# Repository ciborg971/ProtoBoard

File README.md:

# ProtoBoard V0.2

A small board (48 x 56 mm) for great gloves !

* Still a work in progress, current version does NOT work * 

# Features

## Pros :
- ESP32S3 dual core
- Small (48x56 mm)
- Power from 2S to 4S lipo (accept 6.5 volt up to 20 volt)
- Can use Wifi (doesnt use ADC2)
- 16 ADC input
- RGB Header
- 5V 5A for Servo for up to 5 Servo
- Support up to 7 LRA
- Battery protection (integrated BMS : overcharge, overdischarge and overcurrent protection)
- Battery level (via voltage divider)
- Cheap to build
- Use 2.54 mm header
- USB C for programming (The board CANNOT be powered via USB)

## Cons :
- Compoment on both side => more expensive to produce in small quantity in pcb fab (bottom side have easy to solder components)
- Doesnt charge the battery
- PCB is 4 layer (a bit more expensive than 2 layer PCB)

## Buy the PCB

*This design does NOT work right now, do NOT buy it unless you can debug it by yourself*
You can buy the board via PCBWay using the file ProtoBoard.kicad_pcb.zip and the BOM ProtoBoard.xlsx.

## TODO

- Add pinout

## Sponsors

This project is sponsored by PCBWay, thanks to them for their quality PCB + assembly !

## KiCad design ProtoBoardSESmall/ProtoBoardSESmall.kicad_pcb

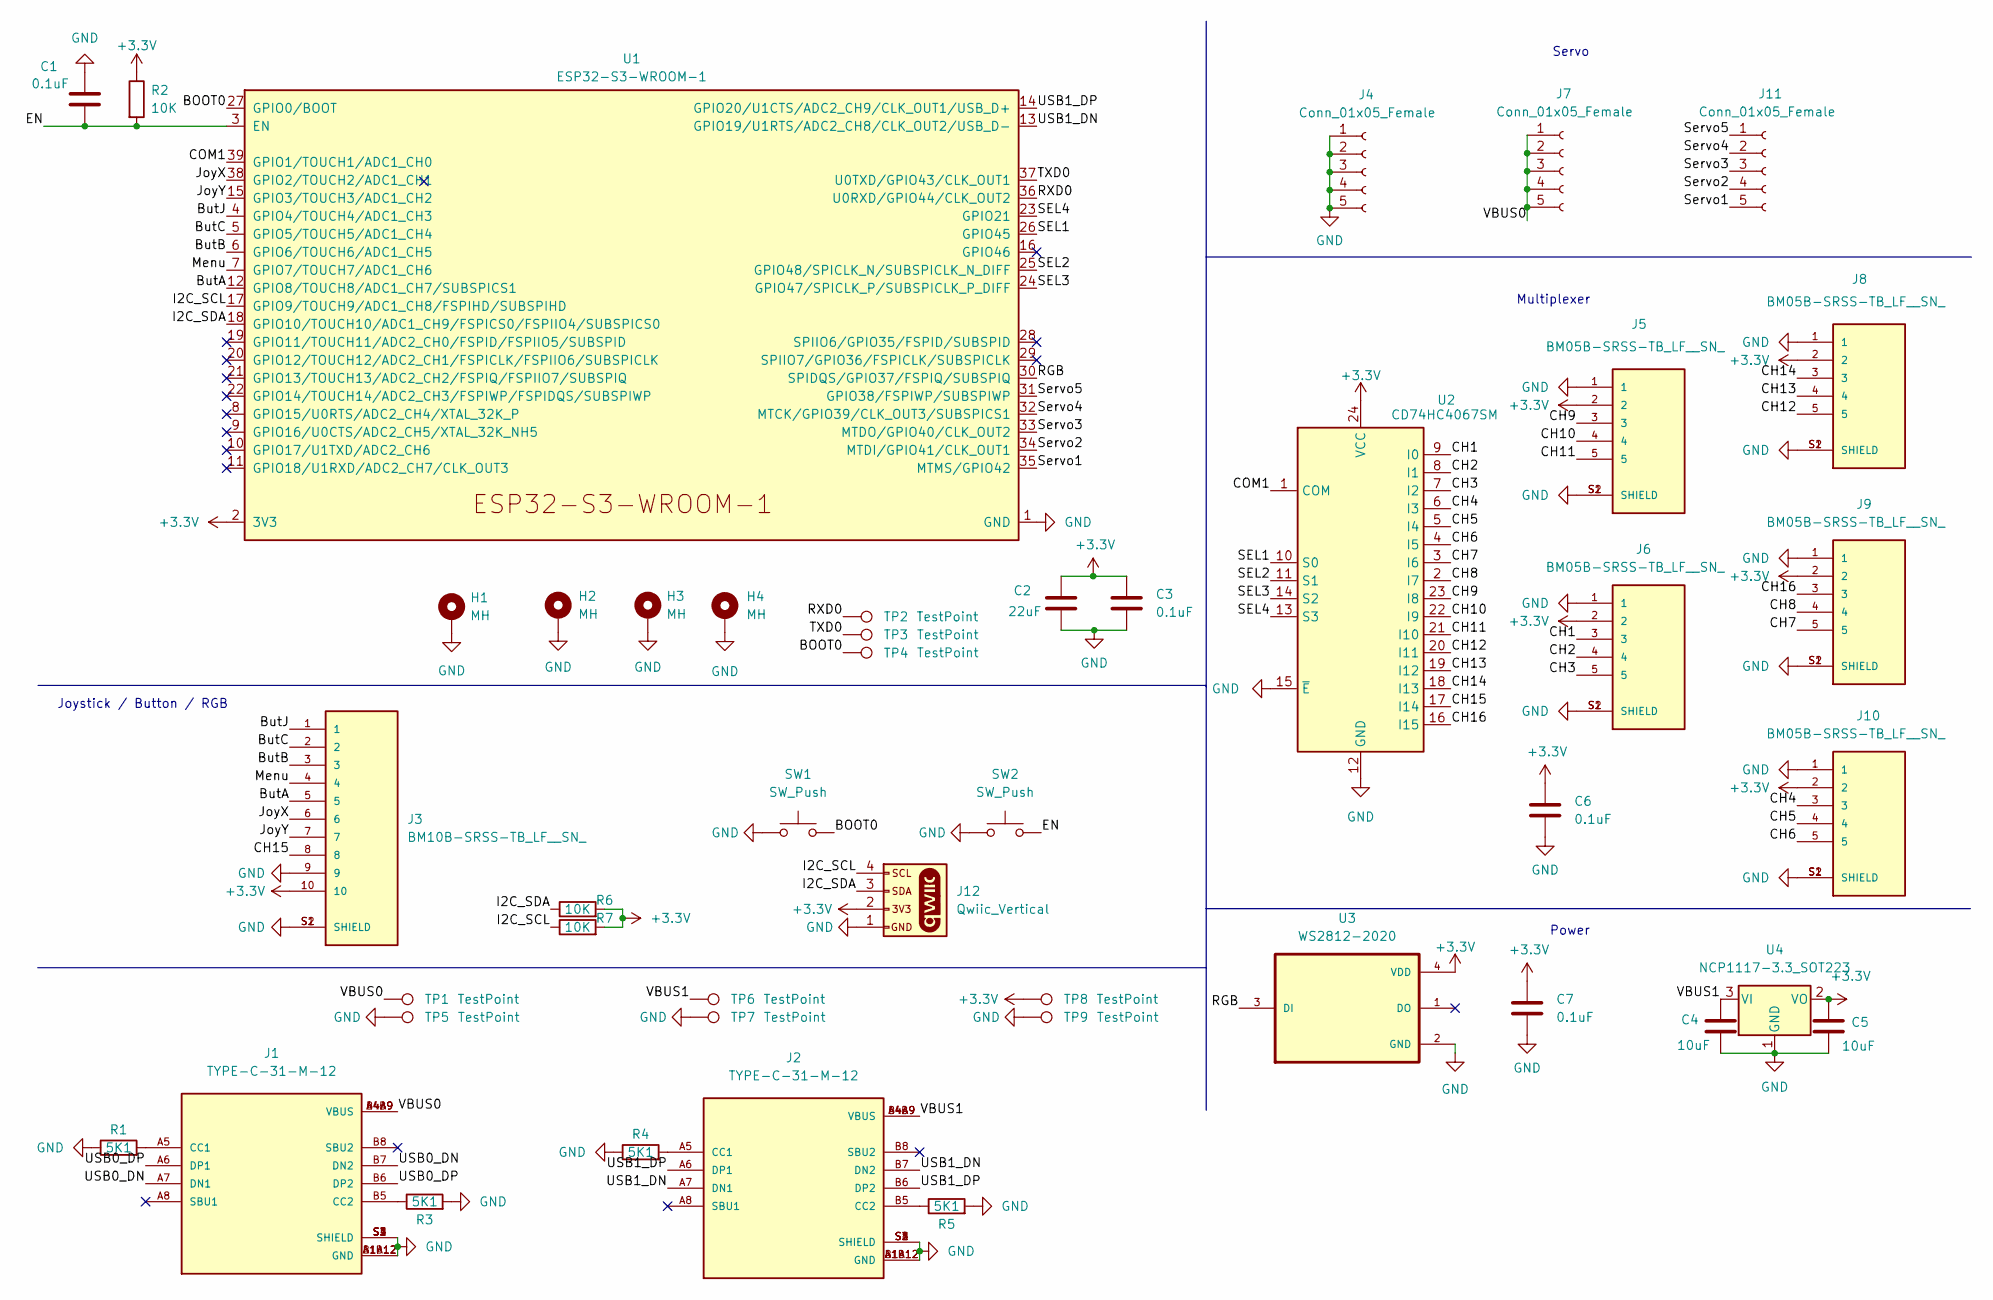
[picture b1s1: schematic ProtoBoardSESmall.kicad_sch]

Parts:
C1, C3, C6, C7: 0.1uF; C_0402_1005Metric; LCSC C129131
C2: 22uF; C_0402_1005Metric; LCSC C415703
C4, C5: 10uF; C_0402_1005Metric; LCSC C315248
H1, H2, H3, H4: MH; MountingHole_2.2mm_M2
J1, J2: TYPE-C-31-M-12; HRO_TYPE-C-31-M-12; PARTREV A; LCSC C165948
J3: BM10B-SRSS-TB_LF__SN_; JST_BM10B-SRSS-TB_LF__SN_; LCSC C160396
J4, J7, J11: Conn_01x05_Female; PinHeader_1x05_P2.54mm_Vertical; LCSC C492404
J5, J6, J8, J9, J10: BM05B-SRSS-TB_LF__SN_; JST_BM05B-SRSS-TB_LF__SN_; LCSC C160391
J12: Qwiic_Vertical; JST04_1MM_Vertical; LCSC C160390
R1, R3, R4, R5: 5K1; R_0402_1005Metric; LCSC C105872
R2: 10K; R_0402_1005Metric; LCSC C427247
R6, R7: 10K; R_0402_1005Metric; LCSC C60490
SW1, SW2: SW_Push; SW_Push_1P1T_NO_CK_KMR2; LCSC C221678
TP1, TP2, TP3, TP4, TP5, TP6, TP7, TP8, TP9: TestPoint; TestPoint_Pad_D1.5mm
U1: ESP32-S3-WROOM-1; LCSC C2913198
U2: CD74HC4067SM; SSOP-24_5.3x8.2mm_P0.65mm; LCSC C496123
U3: WS2812-2020; LED_WS2812-2020; PARTREV V1.3; LCSC C965555
U4: NCP1117-3.3_SOT223; SOT-223-3_TabPin2; LCSC C146799

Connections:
+3V3: C2.1, C3.1, C5.1, C6.1, C7.1, J3.10, J5.2, J6.2, J8.2, J9.2, J10.2, J12.2, R2.1, R6.2, R7.2, TP8.1, U1.2 (3V3), U2.24 (VCC), U3.4 (VDD), U4.2 (VO)
/BOOT0: SW1.2, TP4.1, U1.27 (GPIO0/BOOT)
/ButA: J3.5, U1.12 (GPIO8/TOUCH8/ADC1_CH7/SUBSPICS1)
/ButB: J3.3, U1.6 (GPIO6/TOUCH6/ADC1_CH5)
/ButC: J3.2, U1.5 (GPIO5/TOUCH5/ADC1_CH4)
/ButJ: J3.1, U1.4 (GPIO4/TOUCH4/ADC1_CH3)
/CH1: J6.3, U2.9 (I0)
/CH2: J6.4, U2.8 (I1)
/CH3: J6.5, U2.7 (I2)
/CH4: J10.3, U2.6 (I3)
/CH5: J10.4, U2.5 (I4)
/CH6: J10.5, U2.4 (I5)
/CH7: J9.5, U2.3 (I6)
/CH8: J9.4, U2.2 (I7)
/CH9: J5.3, U2.23 (I8)
/CH10: J5.4, U2.22 (I9)
/CH11: J5.5, U2.21 (I10)
/CH12: J8.5, U2.20 (I11)
/CH13: J8.4, U2.19 (I12)
/CH14: J8.3, U2.18 (I13)
/CH15: J3.8, U2.17 (I14)
/CH16: J9.3, U2.16 (I15)
/COM1: U1.39 (GPIO1/TOUCH1/ADC1_CH0), U2.1 (COM)
/EN: C1.2, R2.2, SW2.2, U1.3 (EN)
/I2C_SCL: J12.4, R7.1, U1.17 (GPIO9/TOUCH9/ADC1_CH8/FSPIHD/SUBSPIHD)
/I2C_SDA: J12.3, R6.1, U1.18 (GPIO10/TOUCH10/ADC1_CH9/FSPICS0/FSPIIO4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)
/JoyX: J3.6, U1.38 (GPIO2/TOUCH2/ADC1_CH1)
/JoyY: J3.7, U1.15 (GPIO3/TOUCH3/ADC1_CH2)
/Menu: J3.4, U1.7 (GPIO7/TOUCH7/ADC1_CH6)
/RGB: U1.30 (SPIDQS/GPIO37/FSPIQ/SUBSPIQ), U3.3 (DI)
/RXD0: TP2.1, U1.36 (U0RXD/GPIO44/CLK_OUT2)
/SEL1: U1.26 (GPIO45), U2.10 (S0)
/SEL2: U1.25 (GPIO48/SPICLK_N/SUBSPICLK_N_DIFF), U2.11 (S1)
/SEL3: U1.24 (GPIO47/SPICLK_P/SUBSPICLK_P_DIFF), U2.14 (S2)
/SEL4: U1.23 (GPIO21), U2.13 (S3)
/Servo1: J11.5, U1.35 (MTMS/GPIO42)
/Servo2: J11.4, U1.34 (MTDI/GPIO41/CLK_OUT1)
/Servo3: J11.3, U1.33 (MTDO/GPIO40/CLK_OUT2)
/Servo4: J11.2, U1.32 (MTCK/GPIO39/CLK_OUT3/SUBSPICS1)
/Servo5: J11.1, U1.31 (GPIO38/FSPIWP/SUBSPIWP)
/TXD0: TP3.1, U1.37 (U0TXD/GPIO43/CLK_OUT1)
/USB0_DN: J1.A7 (DN1), J1.B7 (DN2)
/USB0_DP: J1.A6 (DP1), J1.B6 (DP2)
/USB1_DN: J2.A7 (DN1), J2.B7 (DN2), U1.13 (GPIO19/U1RTS/ADC2_CH8/CLK_OUT2/USB_D-)
/USB1_DP: J2.A6 (DP1), J2.B6 (DP2), U1.14 (GPIO20/U1CTS/ADC2_CH9/CLK_OUT1/USB_D+)
/VBUS0: J1.A4B9 (VBUS), J1.B4A9 (VBUS), J7.1, J7.2, J7.3, J7.4, J7.5, TP1.1
/VBUS1: C4.1, J2.A4B9 (VBUS), J2.B4A9 (VBUS), TP6.1, U4.3 (VI)
GND: C1.1, C2.2, C3.2, C4.2, C5.2, C6.2, C7.2, H1.1, H2.1, H3.1, H4.1, J1.A1B12 (GND), J1.B1A12 (GND), J1.S1 (SHIELD), J1.S2 (SHIELD), J1.S3 (SHIELD), J1.S4 (SHIELD), J2.A1B12 (GND), J2.B1A12 (GND), J2.S1 (SHIELD), J2.S2 (SHIELD), J2.S3 (SHIELD), J2.S4 (SHIELD), J3.9, J3.S1 (SHIELD), J3.S2 (SHIELD), J4.1, J4.2, J4.3, J4.4, J4.5, J5.1, J5.S1 (SHIELD), J5.S2 (SHIELD), J6.1, J6.S1 (SHIELD), J6.S2 (SHIELD), J8.1, J8.S1 (SHIELD), J8.S2 (SHIELD), J9.1, J9.S1 (SHIELD), J9.S2 (SHIELD), J10.1, J10.S1 (SHIELD), J10.S2 (SHIELD), J12.1, R1.1, R3.2, R4.1, R5.2, SW1.1, SW2.1, TP5.1, TP7.1, TP9.1, U1.1 (GND), U1.40 (GND), U1.41 (GND), U2.12 (GND), U2.15 (~E), U3.2 (GND), U4.1 (GND)
unnamed: J1.A5 (CC1), R1.2
unnamed: J1.B5 (CC2), R3.1
unnamed: J2.A5 (CC1), R4.2
unnamed: J2.B5 (CC2), R5.1

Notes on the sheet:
Servo
Joystick / Button / RGB
Multiplexer
Power

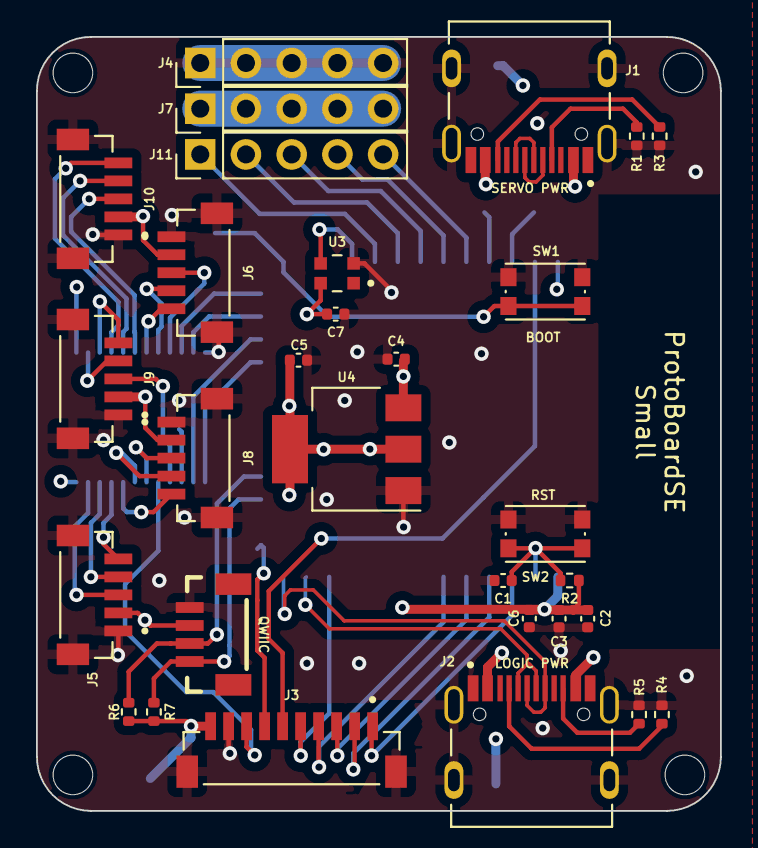
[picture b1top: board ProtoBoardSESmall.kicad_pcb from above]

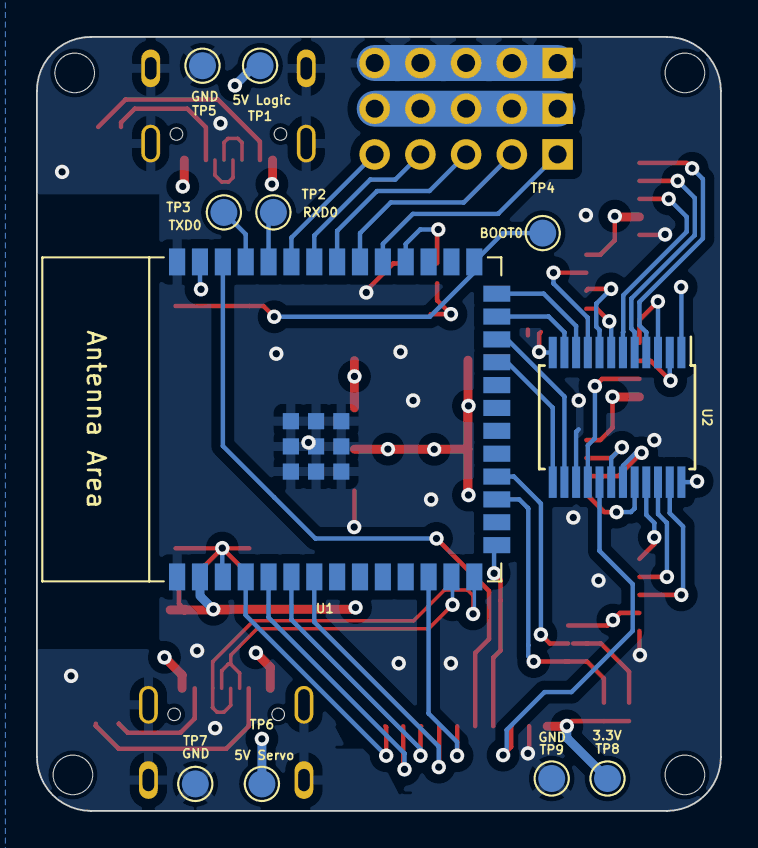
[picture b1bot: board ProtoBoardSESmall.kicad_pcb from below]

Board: 4 copper layers, 38.0 x 43.0 mm, 45 parts (11 on the bottom side), 52 nets.

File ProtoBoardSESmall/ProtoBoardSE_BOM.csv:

Comment,Designator,Footprint,LCSC
"0.1uF","C1,C3,C6","Capacitor_SMD:C_0402_1005Metric","C129131"
"22uF","C2","Capacitor_SMD:C_0402_1005Metric","C415703"
"10uF","C4,C5","Capacitor_SMD:C_0402_1005Metric","C315248"
"MH","H1,H2,H3,H4","MountingHole:MountingHole_2.2mm_M2_Pad",""
"TYPE-C-31-M-12","J1,J2","footprint:HRO_TYPE-C-31-M-12","C165948"
"Conn_01x10_Female","J3","Connector_JST:JST_XH_B10B-XH-AM_1x10_P2.50mm_Vertical","C495726"
"Conn_01x05_Female","J4,J7,J11","Connector_PinHeader_2.54mm:PinHeader_1x05_P2.54mm_Vertical","C492404"
"Conn_01x05","J5,J6,J8,J9,J10","Connector_JST:JST_XH_B5B-XH-AM_1x05_P2.50mm_Vertical","C161872"
"5K1","R1,R3,R4,R5","Resistor_SMD:R_0402_1005Metric","C105872"
"10K","R2","Resistor_SMD:R_0402_1005Metric","C427247"
"SW_Push","SW1,SW2","Button_Switch_SMD:SW_Push_1P1T_NO_CK_KMR2","C221678"
"TestPoint","TP1,TP2,TP3,TP4","TestPoint:TestPoint_Pad_D1.5mm",""
"ESP32-S3-WROOM-1","U1","Espressif:ESP32-S3-WROOM-1","C2913198"
"CD74HC4067SM","U2","Package_SO:SSOP-24_5.3x8.2mm_P0.65mm","C496123"
"NCP1117-3.3_SOT223","U4","Package_TO_SOT_SMD:SOT-223-3_TabPin2","C146799"

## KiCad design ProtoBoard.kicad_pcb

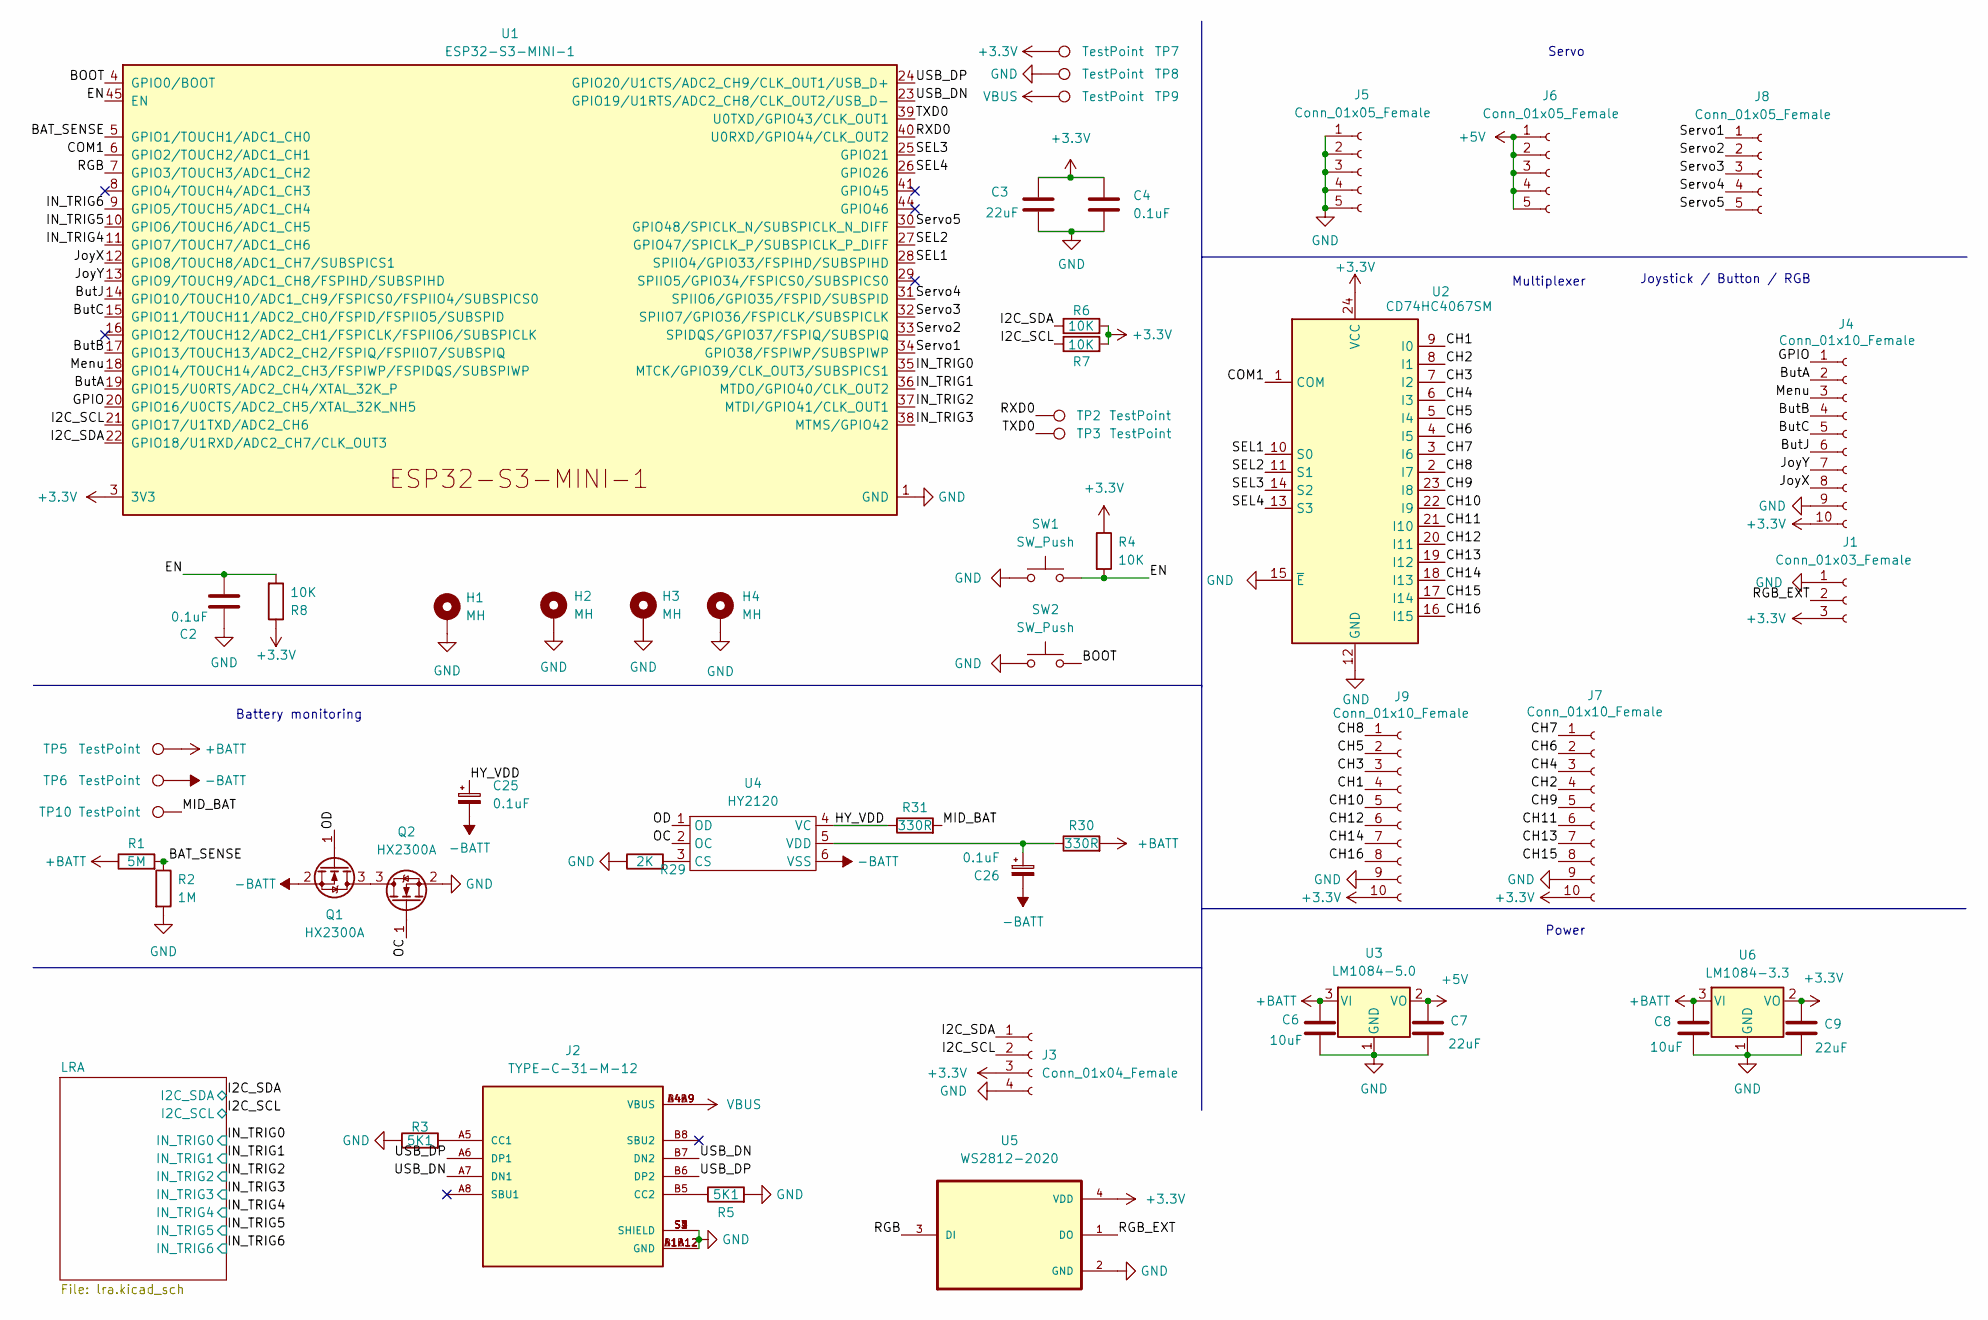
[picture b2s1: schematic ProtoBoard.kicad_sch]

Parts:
C2, C4: 0.1uF; C_0402_1005Metric
C3, C7, C9: 22uF; C_0402_1005Metric
C6, C8: 10uF; C_0402_1005Metric
C25, C26: 0.1uF; CP_Elec_4x5.4; LCSC C271438
H1, H2, H3, H4: MH; MountingHole_2.2mm_M2_Pad
J1: Conn_01x03_Female; PinHeader_1x03_P2.54mm_Vertical
J2: TYPE-C-31-M-12; HRO_TYPE-C-31-M-12; PARTREV A
J3: Conn_01x04_Female; PinHeader_1x04_P2.54mm_Vertical
J4, J7, J9: Conn_01x10_Female; PinHeader_1x10_P2.54mm_Vertical
J5, J6, J8: Conn_01x05_Female; PinHeader_1x05_P2.54mm_Vertical
Q1, Q2: HX2300A; SOT-23; LCSC C296302
R1: 5M; R_0402_1005Metric
R2: 1M; R_0402_1005Metric
R3, R5: 5K1; R_0402_1005Metric
R4, R6, R7, R8: 10K; R_0402_1005Metric
R29: 2K; R_0402_1005Metric
R30, R31: 330R; R_0402_1005Metric
SW1, SW2: SW_Push; SW_Push_SPST_NO_Alps_SKRK
TP2, TP3, TP5, TP6, TP7, TP8, TP9, TP10: TestPoint; TestPoint_Pad_D1.5mm
U1: ESP32-S3-MINI-1
U2: CD74HC4067SM; SSOP-24_5.3x8.2mm_P0.65mm
U3: LM1084-5.0; TO-263-2
U4: HY2120; SOT-23-6
U5: WS2812-2020; LED_WS2812-2020; LCSC C965555
U6: LM1084-3.3; TO-263-2

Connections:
+3V3: C3.1, C4.1, C9.1, J1.3, J3.3, J4.10, J7.10, J9.10, R4.1, R6.2, R7.2, R8.1, TP7.1, U1.3 (3V3), U2.24 (VCC), U5.4 (VDD), U6.2 (VO); also elsewhere on the board
+5V: C7.1, J6.1, J6.2, J6.3, J6.4, J6.5, U3.2 (VO)
+BATT: C6.1, C8.1, R1.1, R30.2, TP5.1, U3.3 (VI), U6.3 (VI)
-BATT: C25.2, C26.2, Q1.2 (S), TP6.1, U4.6 (VSS)
/BAT_SENSE: R1.2, R2.1, U1.5 (GPIO1/TOUCH1/ADC1_CH0)
/BOOT: SW2.2, U1.4 (GPIO0/BOOT)
/ButA: J4.2, U1.19 (GPIO15/U0RTS/ADC2_CH4/XTAL_32K_P)
/ButB: J4.4, U1.17 (GPIO13/TOUCH13/ADC2_CH2/FSPIQ/FSPIIO7/S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)
/ButC: J4.5, U1.15 (GPIO11/TOUCH11/ADC2_CH0/FSPID/FSPIIO5/S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)
/ButJ: J4.6, U1.14 (GPIO10/TOUCH10/ADC1_CH9/FSPICS0/FSPIIO4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)
/CH1: J9.4, U2.9 (I0)
/CH2: J7.4, U2.8 (I1)
/CH3: J9.3, U2.7 (I2)
/CH4: J7.3, U2.6 (I3)
/CH5: J9.2, U2.5 (I4)
/CH6: J7.2, U2.4 (I5)
/CH7: J7.1, U2.3 (I6)
/CH8: J9.1, U2.2 (I7)
/CH9: J7.5, U2.23 (I8)
/CH10: J9.5, U2.22 (I9)
/CH11: J7.6, U2.21 (I10)
/CH12: J9.6, U2.20 (I11)
/CH13: J7.7, U2.19 (I12)
/CH14: J9.7, U2.18 (I13)
/CH15: J7.8, U2.17 (I14)
/CH16: J9.8, U2.16 (I15)
/COM1: U1.6 (GPIO2/TOUCH2/ADC1_CH1), U2.1 (COM)
/EN: C2.2, R4.2, R8.2, SW1.2, U1.45 (EN)
/GPIO: J4.1, U1.20 (GPIO16/U0CTS/ADC2_CH5/XTAL_32K_NH5)
/HY_VDD: C25.1, R31.1, U4.4 (VC)
/I2C_SCL: J3.2, R7.1, U1.21 (GPIO17/U1TXD/ADC2_CH6); also elsewhere on the board
/I2C_SDA: J3.1, R6.1, U1.22 (GPIO18/U1RXD/ADC2_CH7/CLK_OUT3); also elsewhere on the board
/IN_TRIG0: U1.35 (MTCK/GPIO39/CLK_OUT3/SUBSPICS1); also elsewhere on the board
/IN_TRIG1: U1.36 (MTDO/GPIO40/CLK_OUT2); also elsewhere on the board
/IN_TRIG2: U1.37 (MTDI/GPIO41/CLK_OUT1); also elsewhere on the board
/IN_TRIG3: U1.38 (MTMS/GPIO42); also elsewhere on the board
/IN_TRIG4: U1.11 (GPIO7/TOUCH7/ADC1_CH6); also elsewhere on the board
/IN_TRIG5: U1.10 (GPIO6/TOUCH6/ADC1_CH5); also elsewhere on the board
/IN_TRIG6: U1.9 (GPIO5/TOUCH5/ADC1_CH4); also elsewhere on the board
/JoyX: J4.8, U1.12 (GPIO8/TOUCH8/ADC1_CH7/SUBSPICS1)
/JoyY: J4.7, U1.13 (GPIO9/TOUCH9/ADC1_CH8/FSPIHD/SUBSPIHD)
/MID_BAT: R31.2, TP10.1
/Menu: J4.3, U1.18 (GPIO14/TOUCH14/ADC2_CH3/FSPIWP/FSPIDQS/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)
/OC: Q2.1 (G), U4.2 (OC)
/OD: Q1.1 (G), U4.1 (OD)
/RGB: U1.7 (GPIO3/TOUCH3/ADC1_CH2), U5.3 (DI)
/RGB_EXT: J1.2, U5.1 (DO)
/RXD0: TP2.1, U1.40 (U0RXD/GPIO44/CLK_OUT2)
/SEL1: U1.28 (SPIIO4/GPIO33/FSPIHD/SUBSPIHD), U2.10 (S0)
/SEL2: U1.27 (GPIO47/SPICLK_P/SUBSPICLK_P_DIFF), U2.11 (S1)
/SEL3: U1.25 (GPIO21), U2.14 (S2)
/SEL4: U1.26 (GPIO26), U2.13 (S3)
/Servo1: J8.1, U1.34 (GPIO38/FSPIWP/SUBSPIWP)
/Servo2: J8.2, U1.33 (SPIDQS/GPIO37/FSPIQ/SUBSPIQ)
/Servo3: J8.3, U1.32 (SPIIO7/GPIO36/FSPICLK/SUBSPICLK)
/Servo4: J8.4, U1.31 (SPIIO6/GPIO35/FSPID/SUBSPID)
/Servo5: J8.5, U1.30 (GPIO48/SPICLK_N/SUBSPICLK_N_DIFF)
/TXD0: TP3.1, U1.39 (U0TXD/GPIO43/CLK_OUT1)
/USB_DN: J2.A7 (DN1), J2.B7 (DN2), U1.23 (GPIO19/U1RTS/ADC2_CH8/CLK_OUT2/USB_D-)
/USB_DP: J2.A6 (DP1), J2.B6 (DP2), U1.24 (GPIO20/U1CTS/ADC2_CH9/CLK_OUT1/USB_D+)
GND: C2.1, C3.2, C4.2, C6.2, C7.2, C8.2, C9.2, H1.1, H2.1, H3.1, H4.1, J1.1, J2.A1B12 (GND), J2.B1A12 (GND), J2.S1 (SHIELD), J2.S2 (SHIELD), J2.S3 (SHIELD), J2.S4 (SHIELD), J3.4, J4.9, J5.1, J5.2, J5.3, J5.4, J5.5, J7.9, J9.9, Q2.2 (S), R2.2, R3.1, R5.2, R29.1, SW1.1, SW2.1, TP8.1, U1.1 (GND), U1.2 (GND), U1.42 (GND), U1.43 (GND), U1.46 (GND), U1.47 (GND), U1.48 (GND), U1.49 (GND), U1.50 (GND), U1.51 (GND), U1.52 (GND), U1.53 (GND), U1.54 (GND), U1.55 (GND), U1.56 (GND), U1.57 (GND), U1.58 (GND), U1.59 (GND), U1.60 (GND), U1.61 (GND), U1.62 (GND), U1.63 (GND), U1.64 (GND), U1.65 (GND), U2.12 (GND), U2.15 (~E), U3.1 (GND), U5.2 (GND), U6.1 (GND); also elsewhere on the board
unnamed: C26.1, R30.1, U4.5 (VDD)
unnamed: J2.A5 (CC1), R3.2
unnamed: J2.B5 (CC2), R5.1
unnamed: Q1.3 (D), Q2.3 (D)
unnamed: R29.2, U4.3 (CS)
VBUS: J2.A4B9 (VBUS), J2.B4A9 (VBUS), TP9.1

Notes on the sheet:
Multiplexer
Battery monitoring
Power
Joystick / Button / RGB
Servo

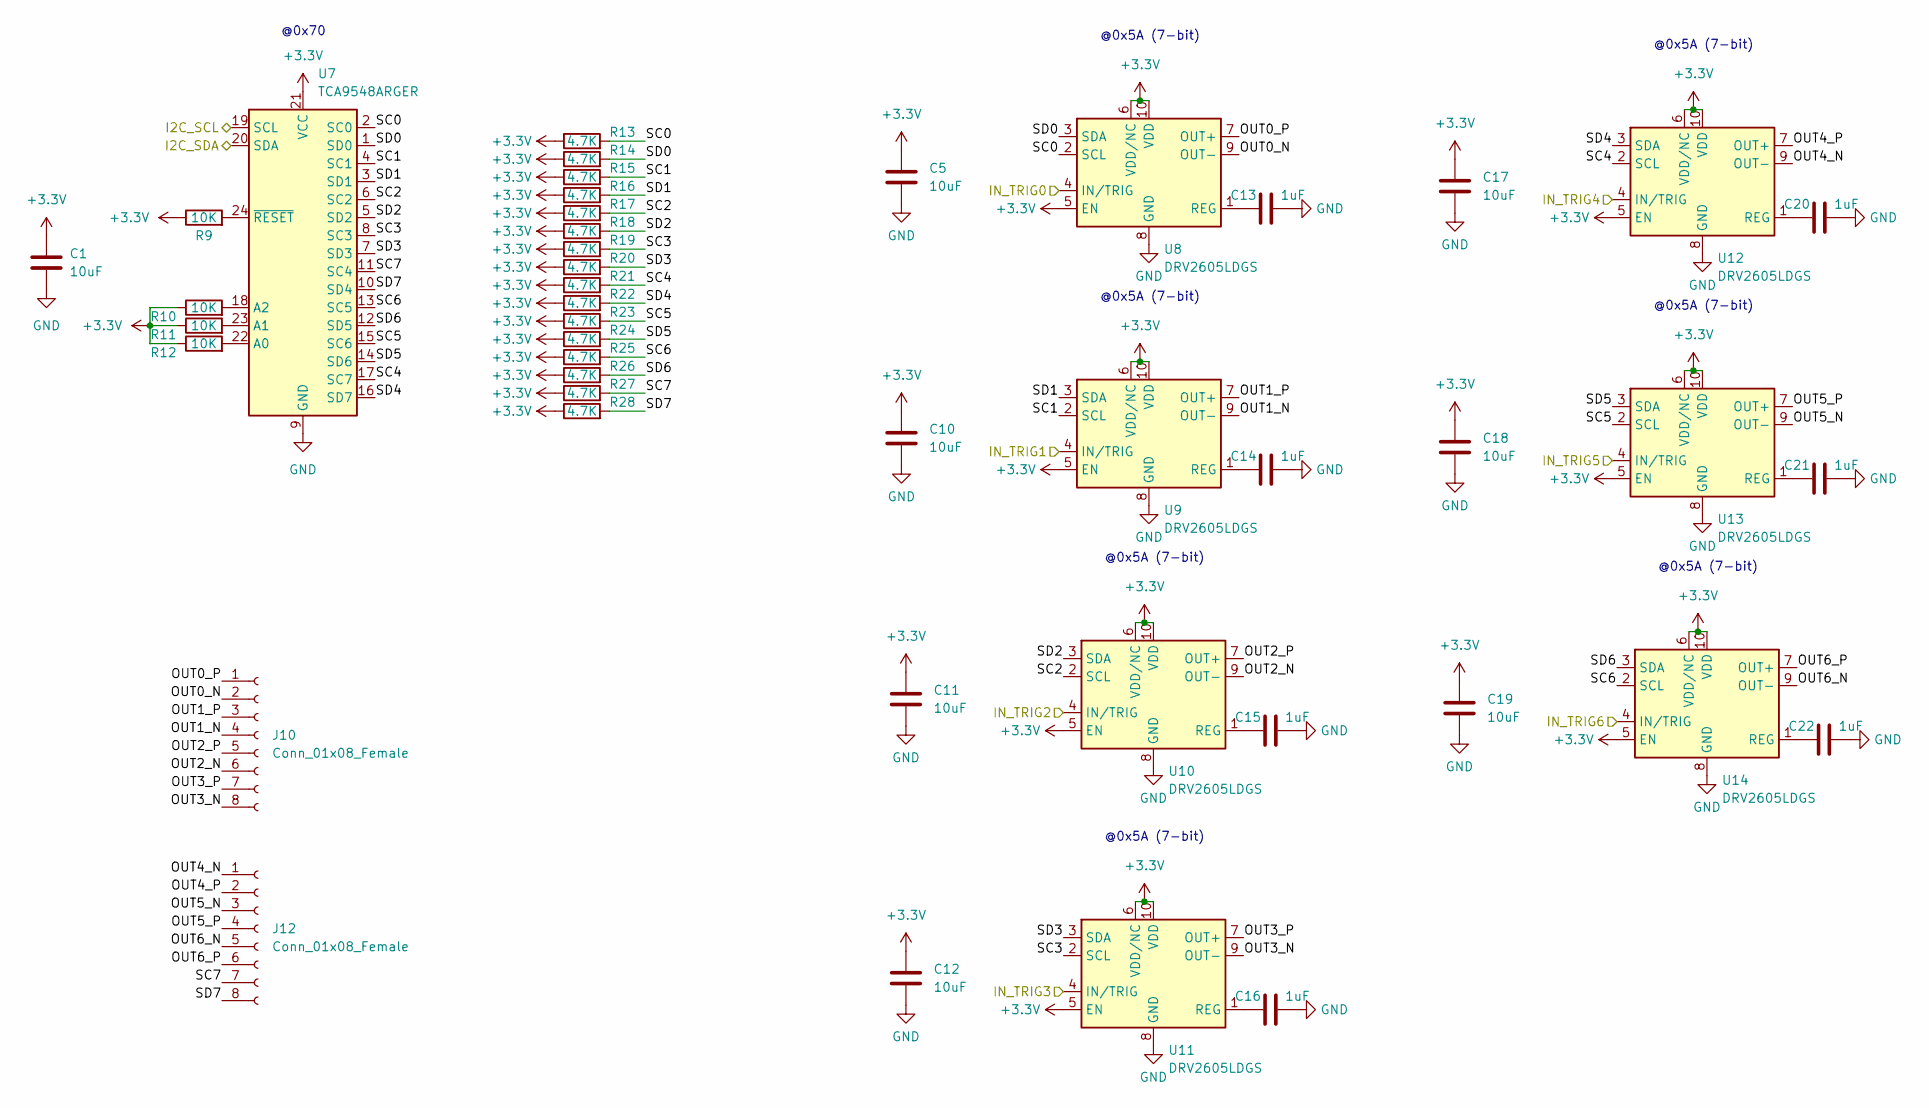
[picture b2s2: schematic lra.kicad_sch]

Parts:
C1, C5, C10, C11, C12, C17, C18, C19: 10uF; C_0402_1005Metric
C13, C14, C15, C16, C20, C21, C22: 1uF; C_0402_1005Metric
J10, J12: Conn_01x08_Female; PinHeader_1x08_P2.54mm_Vertical
R9, R10, R11, R12: 10K; R_0402_1005Metric
R13, R14, R15, R16, R17, R18, R19, R20, R21, R22, R23, R24, R25, R26, R27, R28: 4.7K; R_0402_1005Metric
U7: TCA9548ARGER; Texas_RGE0024C_EP2.1x2.1mm
U8, U9, U10, U11, U12, U13, U14: DRV2605LDGS; VSSOP-10_3x3mm_P0.5mm; LCSC C527464

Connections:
+3V3: C1.1, C5.1, C10.1, C11.1, C12.1, C17.1, C18.1, C19.1, R9.1, R10.1, R11.1, R12.1, R13.1, R14.1, R15.1, R16.1, R17.1, R18.1, R19.1, R20.1, R21.1, R22.1, R23.1, R24.1, R25.1, R26.1, R27.1, R28.1, U7.21 (VCC), U8.5 (EN), U8.6 (VDD/NC), U8.10 (VDD), U9.5 (EN), U9.6 (VDD/NC), U9.10 (VDD), U10.5 (EN), U10.6 (VDD/NC), U10.10 (VDD), U11.5 (EN), U11.6 (VDD/NC), U11.10 (VDD), U12.5 (EN), U12.6 (VDD/NC), U12.10 (VDD), U13.5 (EN), U13.6 (VDD/NC), U13.10 (VDD), U14.5 (EN), U14.6 (VDD/NC), U14.10 (VDD); also elsewhere on the board
/I2C_SCL: U7.19 (SCL); also elsewhere on the board
/I2C_SDA: U7.20 (SDA); also elsewhere on the board
/IN_TRIG0: U8.4 (IN/TRIG); also elsewhere on the board
/IN_TRIG1: U9.4 (IN/TRIG); also elsewhere on the board
/IN_TRIG2: U10.4 (IN/TRIG); also elsewhere on the board
/IN_TRIG3: U11.4 (IN/TRIG); also elsewhere on the board
/IN_TRIG4: U12.4 (IN/TRIG); also elsewhere on the board
/IN_TRIG5: U13.4 (IN/TRIG); also elsewhere on the board
/IN_TRIG6: U14.4 (IN/TRIG); also elsewhere on the board
/LRA/OUT0_N: J10.2, U8.9 (OUT-)
/LRA/OUT0_P: J10.1, U8.7 (OUT+)
/LRA/OUT1_N: J10.4, U9.9 (OUT-)
/LRA/OUT1_P: J10.3, U9.7 (OUT+)
/LRA/OUT2_N: J10.6, U10.9 (OUT-)
/LRA/OUT2_P: J10.5, U10.7 (OUT+)
/LRA/OUT3_N: J10.8, U11.9 (OUT-)
/LRA/OUT3_P: J10.7, U11.7 (OUT+)
/LRA/OUT4_N: J12.1, U12.9 (OUT-)
/LRA/OUT4_P: J12.2, U12.7 (OUT+)
/LRA/OUT5_N: J12.3, U13.9 (OUT-)
/LRA/OUT5_P: J12.4, U13.7 (OUT+)
/LRA/OUT6_N: J12.5, U14.9 (OUT-)
/LRA/OUT6_P: J12.6, U14.7 (OUT+)
/LRA/SC0: R13.2, U7.2 (SC0), U8.2 (SCL)
/LRA/SC1: R15.2, U7.4 (SC1), U9.2 (SCL)
/LRA/SC2: R17.2, U7.6 (SC2), U10.2 (SCL)
/LRA/SC3: R19.2, U7.8 (SC3), U11.2 (SCL)
/LRA/SC4: R21.2, U7.17 (SC7), U12.2 (SCL)
/LRA/SC5: R23.2, U7.15 (SC6), U13.2 (SCL)
/LRA/SC6: R25.2, U7.13 (SC5), U14.2 (SCL)
/LRA/SC7: J12.7, R27.2, U7.11 (SC4)
/LRA/SD0: R14.2, U7.1 (SD0), U8.3 (SDA)
/LRA/SD1: R16.2, U7.3 (SD1), U9.3 (SDA)
/LRA/SD2: R18.2, U7.5 (SD2), U10.3 (SDA)
/LRA/SD3: R20.2, U7.7 (SD3), U11.3 (SDA)
/LRA/SD4: R22.2, U7.16 (SD7), U12.3 (SDA)
/LRA/SD5: R24.2, U7.14 (SD6), U13.3 (SDA)
/LRA/SD6: R26.2, U7.12 (SD5), U14.3 (SDA)
/LRA/SD7: J12.8, R28.2, U7.10 (SD4)
GND: C1.2, C5.2, C10.2, C11.2, C12.2, C13.2, C14.2, C15.2, C16.2, C17.2, C18.2, C19.2, C20.2, C21.2, C22.2, U7.9 (GND), U8.8 (GND), U9.8 (GND), U10.8 (GND), U11.8 (GND), U12.8 (GND), U13.8 (GND), U14.8 (GND); also elsewhere on the board
unnamed: C13.1, U8.1 (REG)
unnamed: C14.1, U9.1 (REG)
unnamed: C15.1, U10.1 (REG)
unnamed: C16.1, U11.1 (REG)
unnamed: C20.1, U12.1 (REG)
unnamed: C21.1, U13.1 (REG)
unnamed: C22.1, U14.1 (REG)
unnamed: R9.2, U7.24 (~RESET)
unnamed: R10.2, U7.18 (A2)
unnamed: R11.2, U7.23 (A1)
unnamed: R12.2, U7.22 (A0)

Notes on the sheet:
@0x5A (7-bit)
@0x70

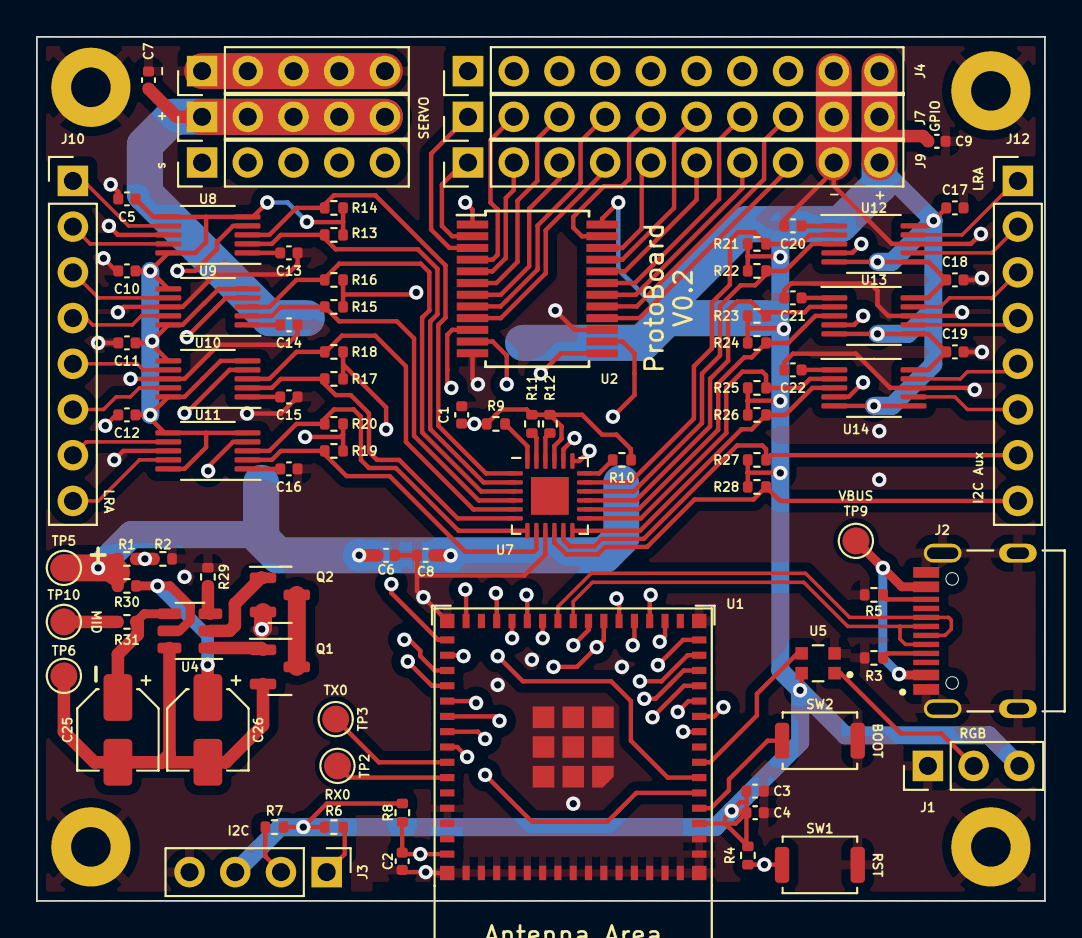
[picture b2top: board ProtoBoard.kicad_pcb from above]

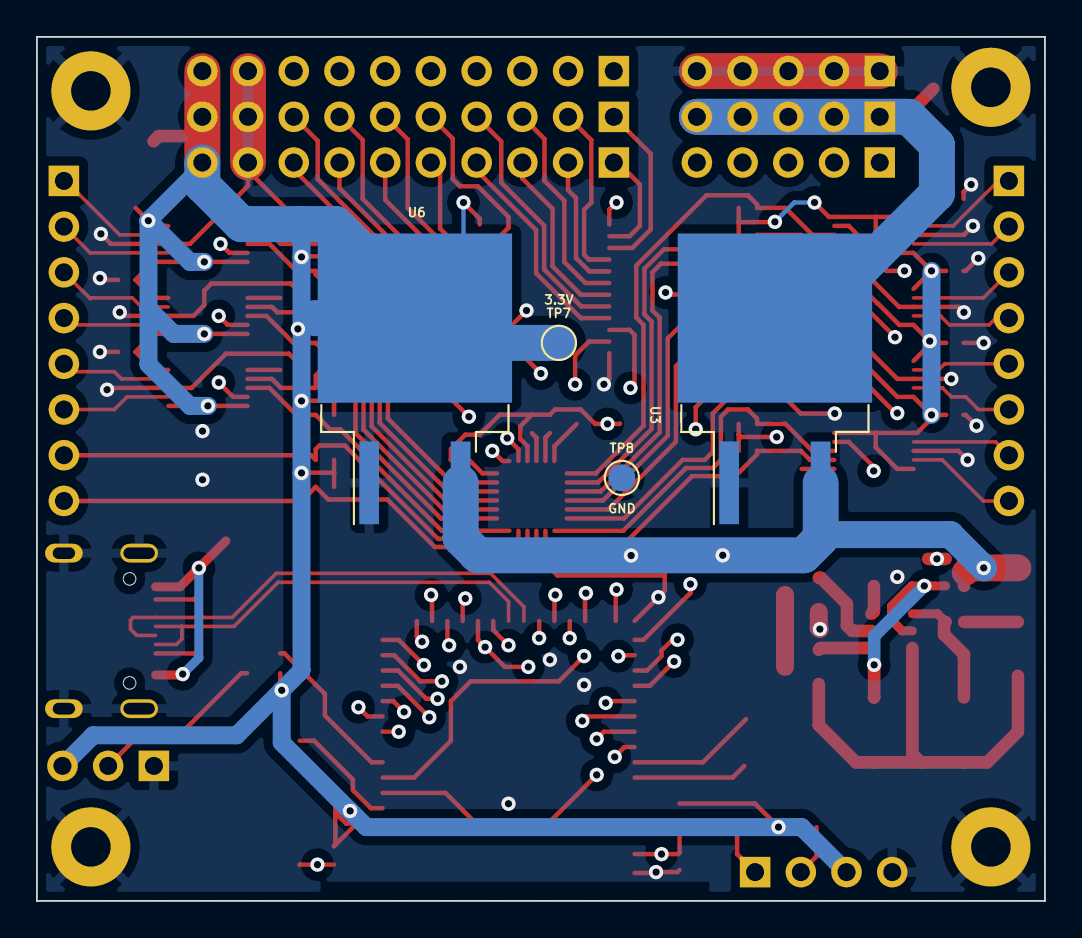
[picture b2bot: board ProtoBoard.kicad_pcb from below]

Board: 4 copper layers, 56.0 x 48.0 mm, 96 parts (4 on the bottom side), 108 nets.

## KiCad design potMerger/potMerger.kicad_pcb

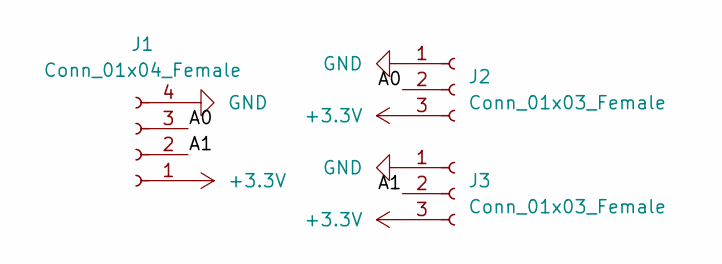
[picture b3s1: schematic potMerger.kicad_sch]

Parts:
J1: Conn_01x04_Female; PinHeader_1x04_P2.00mm_Vertical
J2, J3: Conn_01x03_Female; PinHeader_1x03_P2.00mm_Vertical

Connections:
+3.3V: J1.1, J2.3, J3.3
/A0: J1.3, J2.2
/A1: J1.2, J3.2
GND: J1.4, J2.1, J3.1

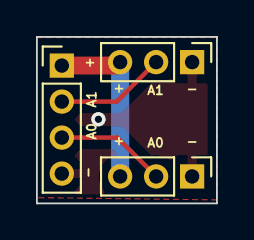
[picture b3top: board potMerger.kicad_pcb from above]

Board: 2 copper layers, 10.0 x 9.2 mm, 3 parts (0 on the bottom side), 4 nets.

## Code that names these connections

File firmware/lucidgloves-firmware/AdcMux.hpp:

#pragma once

#define SEL1 26
#define SEL2 25
#define SEL3 32
#define SEL4 33
#define AdcRead1 35
#define AdcRead2 34

// Maximum number of pin in the ESP32 familly
#define MIN_MUX_GPIO 48

// GPIO from AdcMux is num 49 to 81
// Syntax SEL1, SEL2, SEL3, SEL4, Analog pin to read
int MuxArrRow0[] = {0, 0, 0, 0, AdcRead1};
int MuxArrRow1[] = {0, 0, 0, 0, AdcRead2};
int MuxArrRow2[] = {1, 0, 0, 0, AdcRead1};
int MuxArrRow3[] = {1, 0, 0, 0, AdcRead2};
int MuxArrRow4[] = {0, 1, 0, 0, AdcRead1};
int MuxArrRow5[] = {0, 1, 0, 0, AdcRead2};
int MuxArrRow6[] = {1, 1, 0, 0, AdcRead1};
int MuxArrRow7[] = {1, 1, 0, 0, AdcRead2};
int MuxArrRow8[] = {0, 0, 1, 0, AdcRead1};
int MuxArrRow9[] = {0, 0, 1, 0, AdcRead2};
int MuxArrRow10[] = {1, 0, 1, 0, AdcRead1};
int MuxArrRow11[] = {1, 0, 1, 0, AdcRead2};
int MuxArrRow12[] = {0, 1, 1, 0, AdcRead1};
int MuxArrRow13[] = {0, 1, 1, 0, AdcRead2};
int MuxArrRow14[] = {1, 1, 1, 0, AdcRead1};
int MuxArrRow15[] = {1, 1, 1, 0, AdcRead2};
int MuxArrRow16[] = {0, 0, 0, 1, AdcRead1};
int MuxArrRow17[] = {0, 0, 0, 1, AdcRead2};
int MuxArrRow18[] = {1, 0, 0, 1, AdcRead1};
int MuxArrRow19[] = {1, 0, 0, 1, AdcRead2};
int MuxArrRow20[] = {0, 1, 0, 1, AdcRead1};
int MuxArrRow21[] = {0, 1, 0, 1, AdcRead2};
int MuxArrRow22[] = {1, 1, 0, 1, AdcRead1};
int MuxArrRow23[] = {1, 1, 0, 1, AdcRead2};
int MuxArrRow24[] = {0, 0, 1, 1, AdcRead1};
int MuxArrRow25[] = {0, 0, 1, 1, AdcRead2};
int MuxArrRow26[] = {1, 1, 0, 1, AdcRead1};
int MuxArrRow27[] = {1, 1, 0, 1, AdcRead1};
int MuxArrRow28[] = {0, 0, 1, 1, AdcRead1};
int MuxArrRow29[] = {0, 0, 1, 1, AdcRead2};
int MuxArrRow30[] = {1, 0, 1, 1, AdcRead1};
int MuxArrRow31[] = {1, 0, 1, 1, AdcRead2};
int MuxArrRow32[] = {0, 1, 1, 1, AdcRead1};
int MuxArrRow33[] = {0, 1, 1, 1, AdcRead2};
int MuxArrRow34[] = {1, 1, 1, 1, AdcRead1};
int MuxArrRow35[] = {1, 1, 1, 1, AdcRead2};

int *MuxArr[] = { 
    MuxArrRow0,
    MuxArrRow1,
    MuxArrRow2,
    MuxArrRow3,
    MuxArrRow4,
    MuxArrRow5,
    MuxArrRow6,
    MuxArrRow7,
    MuxArrRow8,
    MuxArrRow9,
    MuxArrRow10,
    MuxArrRow11,
    MuxArrRow12,
    MuxArrRow13,
    MuxArrRow14,
    MuxArrRow15,
    MuxArrRow16,
    MuxArrRow17,
    MuxArrRow18,
    MuxArrRow19,
    MuxArrRow20,
    MuxArrRow21,
    MuxArrRow22,
    MuxArrRow23,
    MuxArrRow24,
    MuxArrRow25,
    MuxArrRow26,
    MuxArrRow27,
    MuxArrRow28,
    MuxArrRow29,
    MuxArrRow30,
    MuxArrRow31,
    MuxArrRow32,
    MuxArrRow33,
    MuxArrRow34,
    MuxArrRow35
};

void SetupAdcMux()
{

  pinMode(SEL1, OUTPUT);
  pinMode(SEL2, OUTPUT);
  pinMode(SEL3, OUTPUT);
  pinMode(SEL4, OUTPUT);
}

int AdcMuxRead(uint8_t pin)
{
    if(pin >= MIN_MUX_GPIO && pin < MIN_MUX_GPIO + 32)
    {
        pin -= MIN_MUX_GPIO;
        digitalWrite(SEL1, MuxArr[pin][0] ? HIGH : LOW);
        digitalWrite(SEL2, MuxArr[pin][1] ? HIGH : LOW);
        digitalWrite(SEL3, MuxArr[pin][2] ? HIGH : LOW);
        digitalWrite(SEL4, MuxArr[pin][3] ? HIGH : LOW);
        delay(1);
        return analogRead(MuxArr[pin][4]);
    }
    else
    {
        return analogRead(pin);
    }
}

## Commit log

2022-04-09 schematic + rooted board
    TODO :
    - Check I2C address
    - Capacitor value for esp32
    - Part sourcing
    - Silkscreen
2022-04-09 add license
2022-04-10 add shunt resistor and set i2c addresses
2022-04-10 add schematic export
2022-04-19 smaller (but more expensive) version board
2022-04-21 Board cleaning progress
2022-04-21 More pcb cleaning
2022-04-21 Remove diode
2022-04-21 Production file + 3D model
2022-04-24 copy firmware from https://github.com/JohnRThomas/FlexiaGloves
2022-04-24 Add multiplexer support
2022-04-24 Implemented mux support for button / finger / joystick + rgb led support
2022-04-24 documentation about multiplexer
2022-04-24 documentation add buying pcb and started updating bom links
2022-05-29 firmware for hw test
2022-12-13 cleaning
2022-12-13 add potMerger : merge cable of 2 potentiometer
2022-12-13 A simpler / cheaper protoboard
2022-12-13 potMerger : made it 0.25 mm wider
2022-12-14 ProtoBoard SE : fix servo connector alignement
2022-12-14 ProtoBoard SE : fix capacitor value and add reset/boot button
2022-12-18 ProtoBoard SE : part sourcing
2022-12-18 ProtoBoard SE : production files for JLCPCB
2023-03-05 Add bms + switch to esp32s3 + USB C + 8 LRA driver
2023-03-05 Routing WIP
2023-03-12 Routing done, silkscreen cleaning, update README, remove old files
2023-03-14 Fix bms + a bit clearer schematic
2023-03-14 Clearing schematic a bit more
2023-03-15 Small PCB layout modification, export schematic.pdf, BOM and production files for PCBWay
2023-05-28 Readme update
2023-09-30 add protoboardSE small edition
2023-10-13 Add lcsc references, routing wip
2023-10-14 Routing done + production files
2023-12-26 ProtoboardSmall : Add QWIIC connector + switch USB C label
